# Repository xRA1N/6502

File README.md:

6502 project

Inspired by Ben eater https://eater.net/6502

arduino mega2560 EEprogramer 
https://github.com/petersieg/eeprom

arduino mega2560 logic monitor
https://github.com/dpm-343/6502-monitor

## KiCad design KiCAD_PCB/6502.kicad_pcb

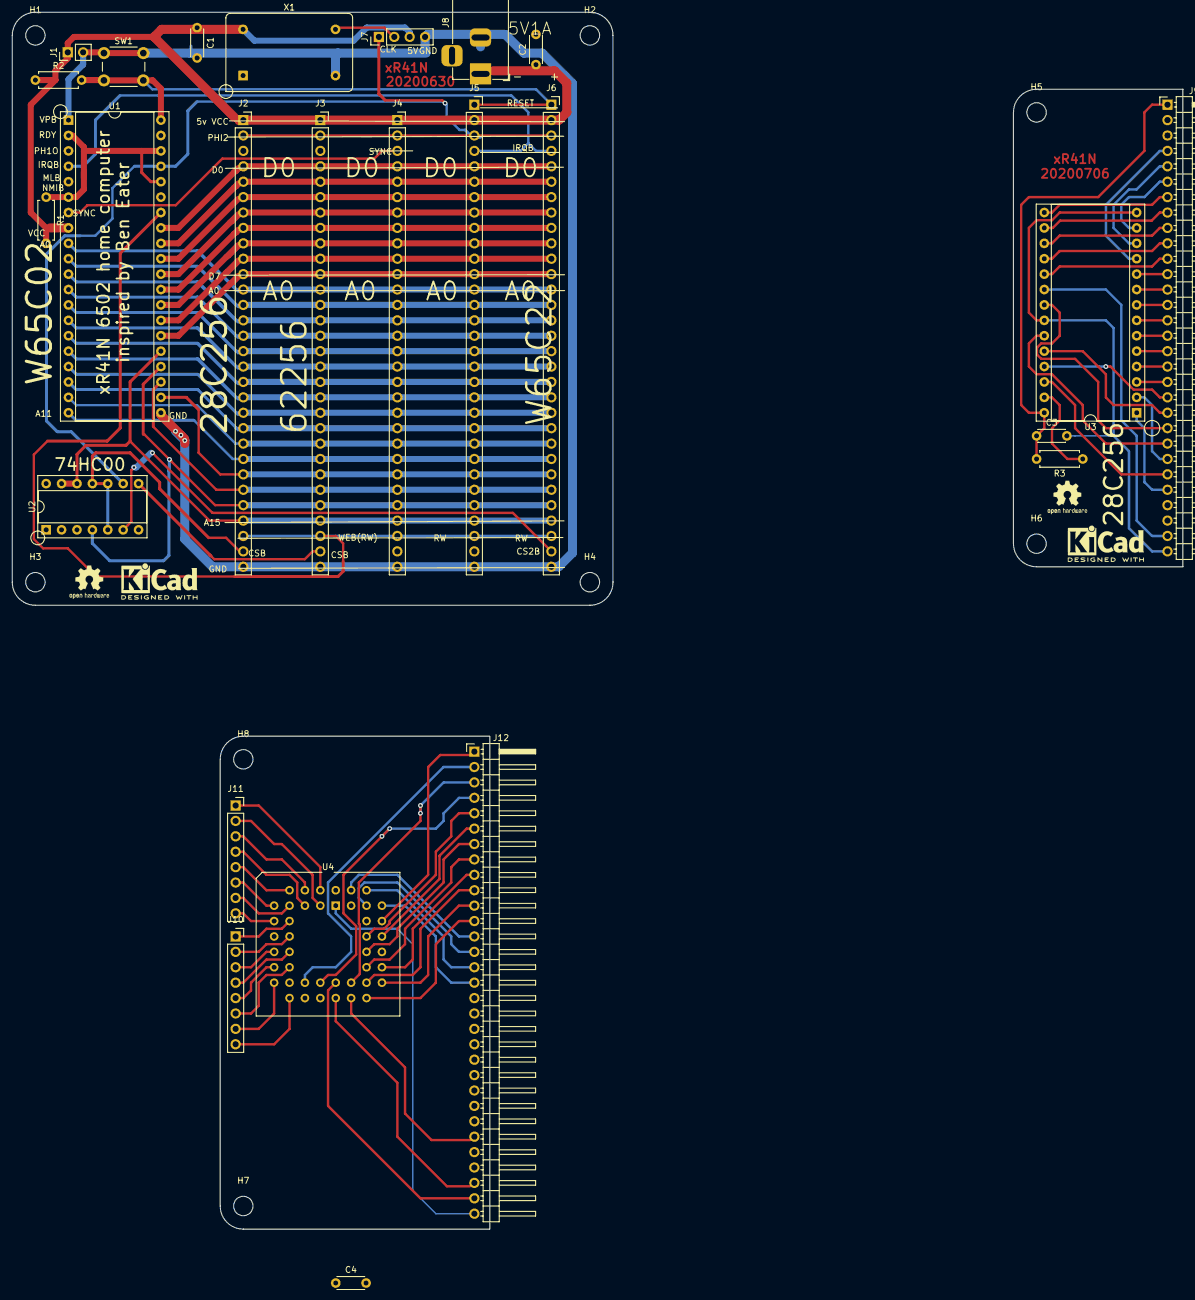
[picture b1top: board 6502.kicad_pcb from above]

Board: 2 copper layers, 193.0 x 200.7 mm, 33 parts (0 on the bottom side), 95 nets.

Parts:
C1, C2, C3, C4: C; C_Disc_D4.3mm_W1.9mm_P5.00mm
H1, H2, H3, H4, H5, H6, H7, H8: MountingHole; MountingHole_3.2mm_M3
J1: Conn_01x02; PinHeader_1x02_P2.54mm_Vertical
J2, J3, J4: Conn_01x30; PinSocket_1x30_P2.54mm_Vertical
J5, J6: Conn_01x31; PinSocket_1x31_P2.54mm_Vertical
J7: Conn_01x04; PinHeader_1x04_P2.54mm_Vertical
J8: Barrel_Jack; BarrelJack_Horizontal
J9: Conn_01x30; PinHeader_1x30_P2.54mm_Horizontal
J10, J11: Conn_01x08; PinSocket_1x08_P2.54mm_Vertical
J12: Conn_01x31; PinHeader_1x31_P2.54mm_Horizontal
R1, R2, R3: R; R_Axial_DIN0207_L6.3mm_D2.5mm_P7.62mm_Horizontal
SW1: SW_Push; SW_PUSH_6mm
U1: 6502; DIP-40_W15.24mm_Socket
U2: 74HC00; DIP-14_W7.62mm_Socket
U3: 28C256; DIP-28_W15.24mm_Socket
U4: W65C22; PLCC-44_THT-Socket
X1: ACO-xxxMHz; Oscillator_DIP-14

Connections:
+5V: C1.1, C2.1, C3.1, J1.1, J2.1, J3.1, J4.1, J5.2, J6.2, J7.3, J8.1, J9.1, J12.2, R1.2, R2.1, R3.2, U1.8, U3.28, U4.21, X1.14
GND: C1.2, C2.2, C3.2, J1.2, J2.30, J3.30, J4.30, J5.31, J6.31, J7.4, J8.2, J9.30, J12.31, SW1.1, U1.1, U1.21, U3.14, U3.22, U4.1, X1.7
unnamed: J2.2, J3.2, J4.2, J5.3, J6.3, J7.1, U1.37, U2.9
unnamed: J2.4, J3.4, J4.4, J5.5, J6.5, U1.33
unnamed: J2.5, J3.5, J4.5, J5.6, J6.6, U1.32
unnamed: J2.6, J3.6, J4.6, J5.7, J6.7, U1.31
unnamed: J2.7, J3.7, J4.7, J5.8, J6.8, U1.30
unnamed: J2.8, J3.8, J4.8, J5.9, J6.9, U1.29
unnamed: J2.9, J3.9, J4.9, J5.10, J6.10, U1.28
unnamed: J2.10, J3.10, J4.10, J5.11, J6.11, U1.27
unnamed: J2.11, J3.11, J4.11, J5.12, J6.12, U1.26
unnamed: J2.12, J3.12, J4.12, J5.13, J6.13, U1.9
unnamed: J2.13, J3.13, J4.13, J5.14, J6.14, U1.10
unnamed: J2.14, J3.14, J4.14, J5.15, J6.15, U1.11
unnamed: J2.15, J3.15, J4.15, J5.16, J6.16, U1.12
unnamed: J2.16, J3.16, J4.16, J5.17, J6.17, U1.13
unnamed: J2.17, J3.17, J4.17, J5.18, J6.18, U1.14
unnamed: J2.18, J3.18, J4.18, J5.19, J6.19, U1.15
unnamed: J2.19, J3.19, J4.19, J5.20, J6.20, U1.16
unnamed: J2.20, J3.20, J4.20, J5.21, J6.21, U1.17
unnamed: J2.21, J3.21, J4.21, J5.22, J6.22, U1.18
unnamed: J2.22, J3.22, J4.22, J5.23, J6.23, U1.19
unnamed: J2.23, J3.23, J4.23, J5.24, J6.24, U1.20
unnamed: J2.24, J3.24, J4.24, J5.25, J6.25, U1.22
unnamed: J2.25, J3.25, J4.25, J5.26, J6.26, U1.23
unnamed: J2.26, J3.26, J4.26, J5.27, J6.27, U1.24, U2.4
unnamed: J2.27, J3.27, J4.27, J5.28, J6.28, U1.25, U2.12, U2.13
unnamed: J2.28, J3.28, J4.28, J5.29, J6.29, U1.34
unnamed: J2.29, U2.5, U2.10, U2.11
unnamed: J3.29, U2.8
unnamed: J4.3, U1.7
unnamed: J5.1, J6.1, R2.2, SW1.2, U1.40
unnamed: J5.4, J6.4, U1.4
unnamed: J6.30, U2.6
unnamed: J7.2, X1.8
unnamed: J9.4, U3.11
unnamed: J9.5, U3.12
unnamed: J9.6, U3.13
unnamed: J9.7, U3.15
unnamed: J9.8, U3.16
unnamed: J9.9, U3.17
unnamed: J9.10, U3.18
unnamed: J9.11, U3.19
unnamed: J9.12, U3.10
unnamed: J9.13, U3.9
unnamed: J9.14, U3.8
unnamed: J9.15, U3.7
unnamed: J9.16, U3.6
unnamed: J9.17, U3.5
unnamed: J9.18, U3.4
unnamed: J9.19, U3.3
unnamed: J9.20, U3.25
unnamed: J9.21, U3.24
unnamed: J9.22, U3.21
unnamed: J9.23, U3.23
unnamed: J9.24, U3.2
unnamed: J9.25, U3.26
unnamed: J9.26, U3.1
unnamed: J9.28, R3.1, U3.27
unnamed: J9.29, U3.20
unnamed: J10.1, U4.10
unnamed: J10.2, U4.12
unnamed: J10.3, U4.13
unnamed: J10.4, U4.14
unnamed: J10.5, U4.15
unnamed: J10.6, U4.16
unnamed: J10.7, U4.17
unnamed: J10.8, U4.18
unnamed: J11.1, U4.2
unnamed: J11.2, U4.3
unnamed: J11.3, U4.4
unnamed: J11.4, U4.5
unnamed: J11.5, U4.6
unnamed: J11.6, U4.7
unnamed: J11.7, U4.8
unnamed: J11.8, U4.9
unnamed: J12.1, U4.37
unnamed: J12.3, U4.27
unnamed: J12.4, U4.23
unnamed: J12.5, U4.36
unnamed: J12.6, U4.35
unnamed: J12.7, U4.34
unnamed: J12.8, U4.32
unnamed: J12.9, U4.31
unnamed: J12.10, U4.30
unnamed: J12.11, U4.29
unnamed: J12.12, U4.28
unnamed: J12.13, U4.42
unnamed: J12.14, U4.41
unnamed: J12.15, U4.40
unnamed: J12.16, U4.39
unnamed: J12.26, U4.26
unnamed: J12.29, U4.24
unnamed: J12.30, U4.25
unnamed: R1.1, U1.2, U1.6, U1.36, U1.38
